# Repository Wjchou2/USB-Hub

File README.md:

# Endless' USB HUB

A compact custom USB 2.0 hub PCB based on the USB2514B controller. It features two USB-A ports and a 4-pin header breakout for easy integration with embedded systems or custom hardware projects.
Simply use a USB-C to C cable to plug the hub into your computer, and check that the LED indicator is on. Then connect any USB-A devices and they will show up on your computer.
I made this project because I have a Mac and never seem to have enough adapters, I also find that I use 4 pin headers often when tinkering with microcontrollers, so I added an easy access 4 pin header integrated into the hub. 

<br>
<br>
No firmware needed!

BOM:
| Designator  | Footprint                                               | Quantity | Designation                 | Link                                                                                                       | Cost   | Total Cost |
|-------------|---------------------------------------------------------|----------|-----------------------------|------------------------------------------------------------------------------------------------------------|--------|------------|
| U2          | SOT-223                                                 | 1        | AMS1117-3.3                 | https://www.lcsc.com/product-detail/C6186.html?s_z=n_AMS1117-3.3                                           | 0.1876 | 0.1876     |
| R3          | R_0603_1608Metric_Pad0.98x0.95mm_HandSolder             | 1        | 12k                         | https://www.lcsc.com/product-detail/C2906989.html?s_z=n_12k%25201%2525%25200603                            | 0.001  | 0.001      |
| R7,R6,R8,R9 | R_0603_1608Metric_Pad0.98x0.95mm_HandSolder             | 4        | 10k                         | https://www.lcsc.com/product-detail/C98220.html?s_z=n_10k%25201%2525%25200603                              | 0.0013 | 0.0052     |
| J2,J3       | USB_A_Receptacle_GCT_USB1046                            | 2        | USB_A                       | https://www.lcsc.com/product-detail/C6307429.html?s_z=n_USB1046                                            | 1.1405 | 2.281      |
| C2,C1,C7    | C_0805_2012Metric_Pad1.18x1.45mm_HandSolder             | 3        | 0.1µ                        | https://www.lcsc.com/product-detail/C53084456.html?s_z=n_100%2520nF%252050V%2520X7R%25200805               | 0.0018 | 0.0054     |
| C4,C3       | C_0603_1608Metric_Pad1.08x0.95mm_HandSolder             | 2        | 22 pF                       | https://www.lcsc.com/product-detail/C695385.html?s_z=n_22%2520pF%2520NPO%25200603                          | 0.051  | 0.102      |
| Y1          | Crystal_SMD_3225-4Pin_3.2x2.5mm                         | 1        | 12.000 MHz                  | https://www.lcsc.com/product-detail/C1647.html?s_z=n_18%2520pF%2520crysta                                  | 0.3272 | 0.3272     |
| J5          | PinHeader_1x04_P2.54mm_Vertical                         | 1        | Conn_01x04_Socket           | https://www.lcsc.com/product-detail/C52016392.html?s_z=n_Pin%2520Header%25201x04%25202.54mm                | 0.0171 | 0.0171     |
| R2,R1       | R_0603_1608Metric_Pad0.98x0.95mm_HandSolder             | 2        | 5.1k                        | https://www.lcsc.com/search?q=5.1k%25201%2525%25200603&s_z=n_5.1k%25201%2525%25200603                      | 0.0012 | 0.0024     |
| R4,R5       | R_0603_1608Metric_Pad0.98x0.95mm_HandSolder             | 2        | 100k                        | https://www.lcsc.com/product-detail/C14675.html?s_z=n_100k%25201%2525%25200603                             | 0.0013 | 0.0026     |
| C6,C5       | C_1206_3216Metric_Pad1.33x1.80mm_HandSolder             | 2        | 10 µF                       | https://www.lcsc.com/product-detail/C342827.html?s_z=n_10%2520uF%252016V%2520X7R%25201206                  | 0.0897 | 0.1794     |
| F1          | Fuse_1812_4532Metric_Pad1.30x3.40mm_HandSolder          | 1        | 0.5A                        | https://www.lcsc.com/product-detail/C7542969.html?s_z=n_PTC%2520fuse%25200.5A%25201812                     | 0.0403 | 0.0403     |
| J1          | USB_C_Receptacle_GCT_USB4105-xx-A_16P_TopMnt_Horizontal | 1        | USB_C_Receptacle_USB2.0_16P | https://www.lcsc.com/product-detail/C2988369.html?s_z=n_USB%2520C%2520receptacle%252016P%2520top%2520mount | 0.0829 | 0.0829     |
| U1          | QFN-36-1EP_6x6mm_P0.5mm_EP3.7x3.7mm                     | 1        | USB2514B_Bi                 | https://www.lcsc.com/product-detail/C220807.html?s_z=n_USB2514B%2520USB%2520hub%25204-port%2520Octopart    | 2.7952 | 2.7952     |
| R10         | R_0603_1608Metric_Pad0.98x0.95mm_HandSolder             | 1        | 1.5kΩ                       | https://www.lcsc.com/product-detail/C22843.html?s_z=n_1.5k%25201%2525%25200603                             | 0.0012 | 0.0012     |
| D1          | LED_0201_0603Metric_Pad0.64x0.40mm_HandSolder           | 1        | LED                         | https://www.lcsc.com/search?q=LED%25200603%2520Green&s_z=n_LED%25200603%2520Green                          | 0.0667 | 0.0667     |
|             |                                                         |          |                             |                                                                                                            |        | 6.0972     |

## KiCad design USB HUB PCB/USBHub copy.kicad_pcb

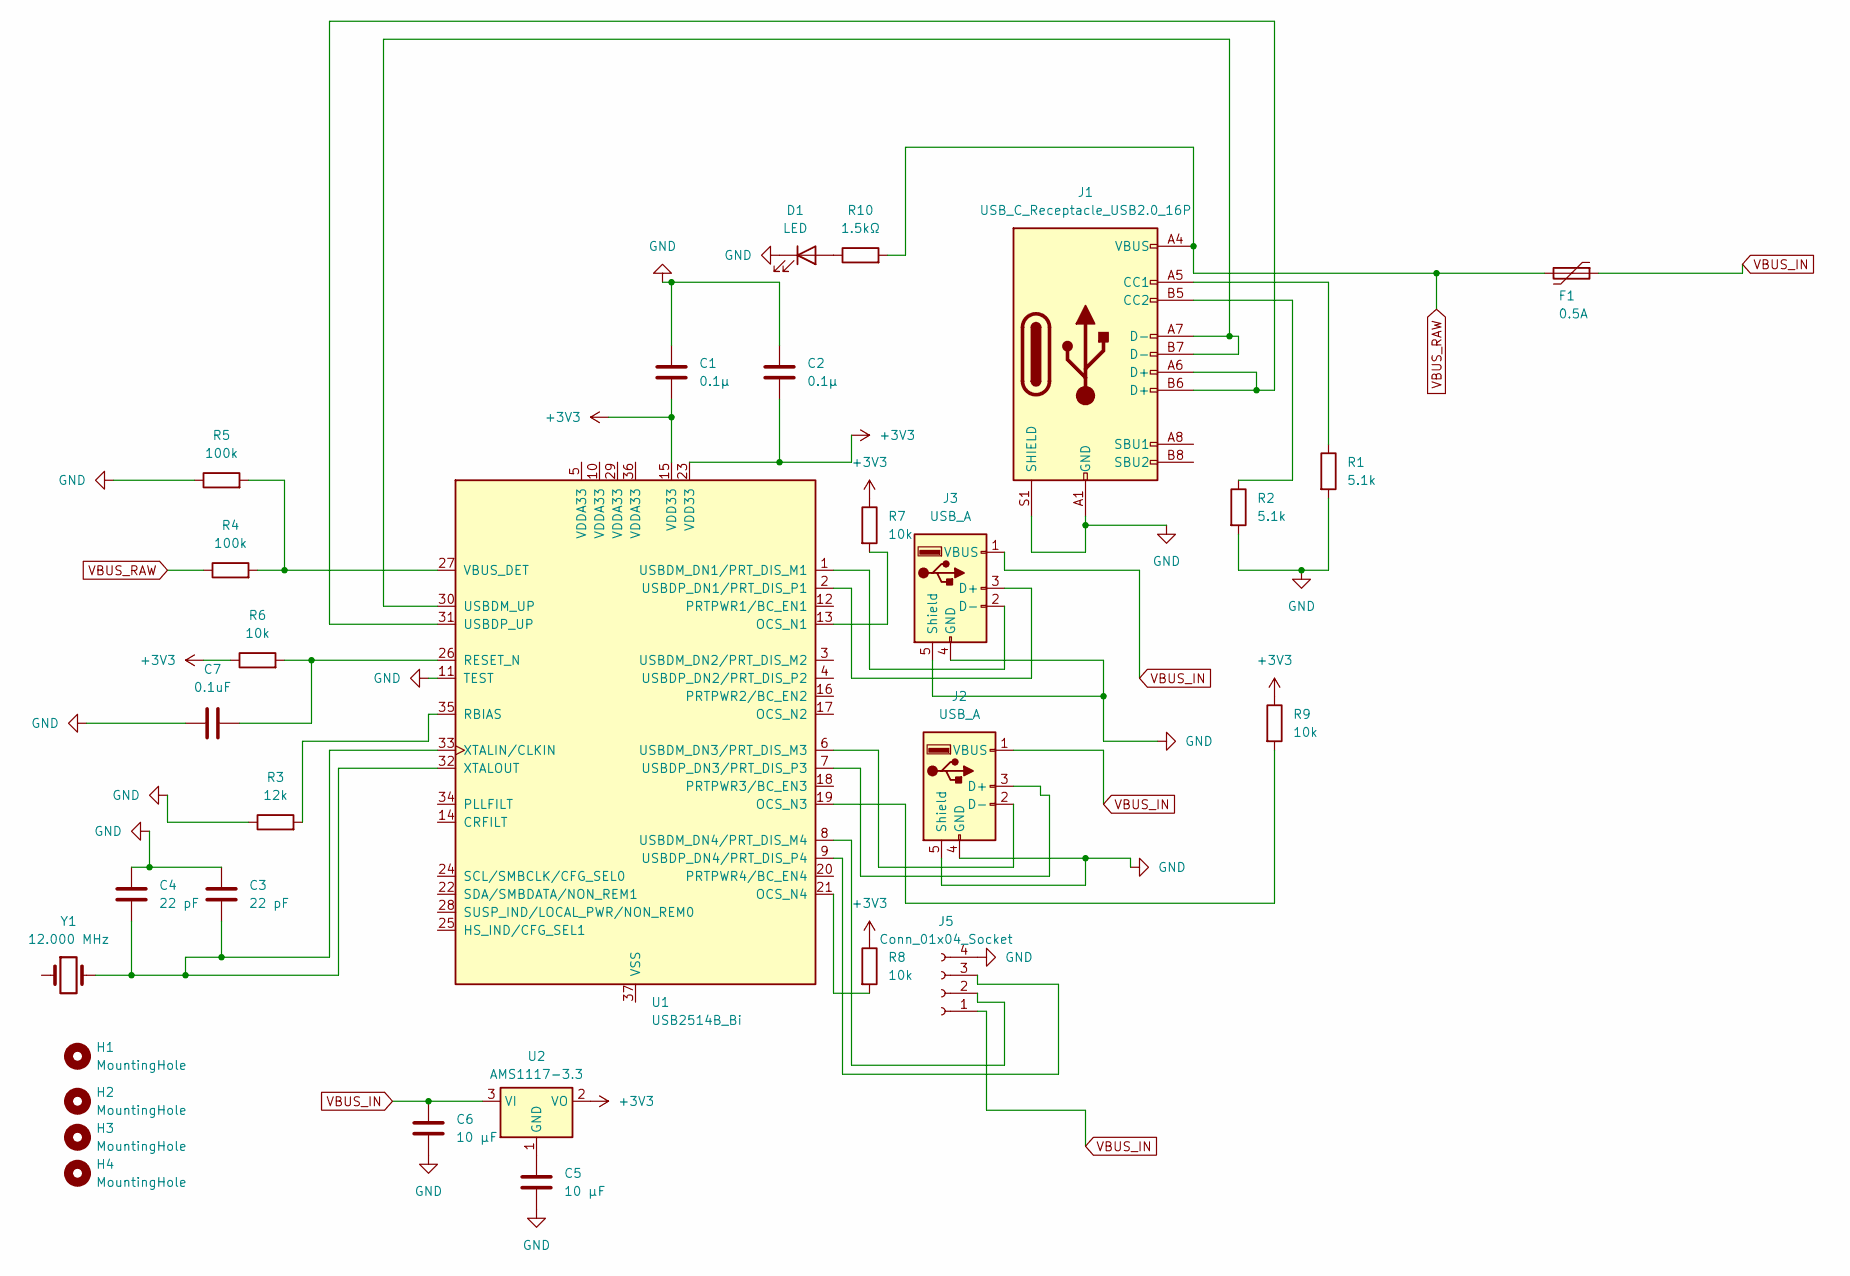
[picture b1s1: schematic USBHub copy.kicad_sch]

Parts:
C1, C2: 0.1µ; C_0805_2012Metric_Pad1.18x1.45mm_HandSolder
C3, C4: 22 pF; C_0603_1608Metric_Pad1.08x0.95mm_HandSolder
C5, C6: 10 µF; C_1206_3216Metric_Pad1.33x1.80mm_HandSolder
C7: 0.1uF; C_0805_2012Metric_Pad1.18x1.45mm_HandSolder
D1: LED; LED_0201_0603Metric_Pad0.64x0.40mm_HandSolder
F1: 0.5A; Fuse_1812_4532Metric_Pad1.30x3.40mm_HandSolder
H1, H2, H3, H4: MountingHole; MountingHole_2.2mm_M2
J1: USB_C_Receptacle_USB2.0_16P; USB_C_Receptacle_GCT_USB4105-xx-A_16P_TopMnt_Horizontal
J2, J3: USB_A; USB_A_Receptacle_GCT_USB1046
J5: Conn_01x04_Socket; PinHeader_1x04_P2.54mm_Vertical
R1, R2: 5.1k; R_0603_1608Metric_Pad0.98x0.95mm_HandSolder
R3: 12k; R_0603_1608Metric_Pad0.98x0.95mm_HandSolder
R4, R5: 100k; R_0603_1608Metric_Pad0.98x0.95mm_HandSolder
R6, R7, R8, R9: 10k; R_0603_1608Metric_Pad0.98x0.95mm_HandSolder
R10: 1.5kΩ; R_0603_1608Metric_Pad0.98x0.95mm_HandSolder
U1: USB2514B_Bi; QFN-36-1EP_6x6mm_P0.5mm_EP3.7x3.7mm
U2: AMS1117-3.3; SOT-223
Y1: 12.000 MHz; Crystal_SMD_3225-4Pin_3.2x2.5mm

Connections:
+3V3: C1.2, C2.2, R6.1, R7.1, R8.1, R9.1, U1.15 (VDD33), U1.23 (VDD33), U2.2 (VO)
GND: C1.1, C2.1, C3.1, C4.1, C5.2, C6.2, C7.1, D1.1 (K), J1.A1 (GND), J1.A12 (GND), J1.B1 (GND), J1.B12 (GND), J1.S1 (SHIELD), J2.4 (GND), J2.5 (Shield), J3.4 (GND), J3.5 (Shield), J5.4, R1.2, R2.2, R3.1, R5.1, U1.11 (TEST)
unnamed: D1.2 (A), R10.1
unnamed: J1.A5 (CC1), R1.1
unnamed: J1.B5 (CC2), R2.1
unnamed: J2.3 (D+), U1.7 (USBDP_DN3/PRT_DIS_P3)
unnamed: J2.2 (D-), U1.6 (USBDM_DN3/PRT_DIS_M3)
unnamed: J3.3 (D+), U1.2 (USBDP_DN1/PRT_DIS_P1)
unnamed: J3.2 (D-), U1.1 (USBDM_DN1/PRT_DIS_M1)
unnamed: J5.2, U1.8 (USBDM_DN4/PRT_DIS_M4)
unnamed: J5.3, U1.9 (USBDP_DN4/PRT_DIS_P4)
unnamed: R7.2, U1.13 (OCS_N1)
unnamed: R9.2, U1.19 (OCS_N3)
unnamed: R8.2, U1.21 (OCS_N4)
unnamed: R3.2, U1.35 (RBIAS)
unnamed: C7.2, R6.2, U1.26 (RESET_N)
unnamed: J1.A7 (D-), J1.B7 (D-), U1.30 (USBDM_UP)
unnamed: J1.A6 (D+), J1.B6 (D+), U1.31 (USBDP_UP)
unnamed: R4.2, R5.2, U1.27 (VBUS_DET)
unnamed: C3.2, C4.2, U1.32 (XTALOUT), U1.33 (XTALIN/CLKIN), Y1.2
unnamed: C5.1, U2.1 (GND)
VBUS_IN: C6.1, F1.1, J2.1 (VBUS), J3.1 (VBUS), J5.1, U2.3 (VI)
VBUS_RAW: F1.2, J1.A4 (VBUS), J1.A9 (VBUS), J1.B4 (VBUS), J1.B9 (VBUS), R4.1, R10.2

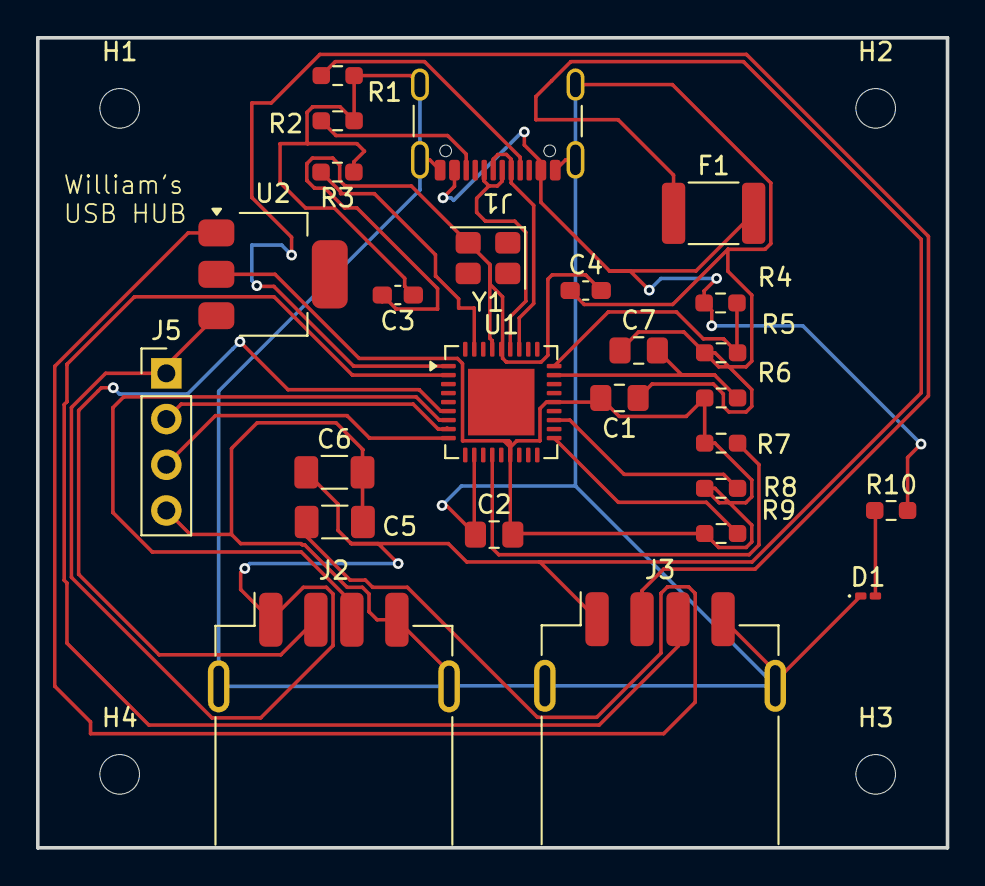
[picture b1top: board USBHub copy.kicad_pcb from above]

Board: 2 copper layers, 50.5 x 45.0 mm, 30 parts (0 on the bottom side), 23 nets.

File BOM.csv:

"","Designator","Footprint","Quantity","Designation","Link","Cost","Total Cost",""
"","-------------","---------------------------------------------------------","----------","-----------------------------","------------------------------------------------------------------------------------------------------------","--------","------------",""
"","U2","SOT-223","1","AMS1117-3.3","https://www.lcsc.com/product-detail/C6186.html?s_z=n_AMS1117-3.3","0.1876","0.1876",""
"","R3","R_0603_1608Metric_Pad0.98x0.95mm_HandSolder","1","12k","https://www.lcsc.com/product-detail/C2906989.html?s_z=n_12k%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","0.001","0.001",""
"","R7,R6,R8,R9","R_0603_1608Metric_Pad0.98x0.95mm_HandSolder","4","10k","https://www.lcsc.com/product-detail/C98220.html?s_z=n_10k%25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","0.0013","0.0052",""
"","J2,J3","USB_A_Receptacle_GCT_USB1046","2","USB_A","https://www.lcsc.com/product-detail/C6307429.html?s_z=n_USB1046","1.1405","2.281",""
"","C2,C1,C7","C_0805_2012Metric_Pad1.18x1.45mm_HandSolder","3","0.1µ","https://www.lcsc.com/product-detail/C53084456.html?s_z=n_100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","0.0018","0.0054",""
"","C4,C3","C_0603_1608Metric_Pad1.08x0.95mm_HandSolder","2","22 pF","https://www.lcsc.com/product-detail/C695385.html?s_z=n_22%25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","0.051","0.102",""
"","Y1","Crystal_SMD_3225-4Pin_3.2x2.5mm","1","12.000 MHz","https://www.lcsc.com/product-detail/C1647.html?s_z=n_18%2520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","0.3272","0.3272",""
"","J5","PinHeader_1x04_P2.54mm_Vertical","1","Conn_01x04_Socket","https://www.lcsc.com/product-detail/C52016392.html?s_z=n_Pin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","0.0171","0.0171",""
"","R2,R1","R_0603_1608Metric_Pad0.98x0.95mm_HandSolder","2","5.1k","https://www.lcsc.com/search?q=5.1k%25201%2525%25200603&s_z=n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","0.0012","0.0024",""
"","R4,R5","R_0603_1608Metric_Pad0.98x0.95mm_HandSolder","2","100k","https://www.lcsc.com/product-detail/C14675.html?s_z=n_100k%2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","0.0013","0.0026",""
"","C6,C5","C_1206_3216Metric_Pad1.33x1.80mm_HandSolder","2","10 µF","https://www.lcsc.com/product-detail/C342827.html?s_z=n_10%25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","0.0897","0.1794",""
"","F1","Fuse_1812_4532Metric_Pad1.30x3.40mm_HandSolder","1","0.5A","https://www.lcsc.com/product-detail/C7542969.html?s_z=n_PTC%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","0.0403","0.0403",""
"","J1","USB_C_Receptacle_GCT_USB4105-xx-A_16P_TopMnt_Horizontal","1","USB_C_Receptacle_USB2.0_16P","https://www.lcsc.com/product-detail/C2988369.html?s_z=n_USB%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","0.0829","0.0829",""
"","U1","QFN-36-1EP_6x6mm_P0.5mm_EP3.7x3.7mm","1","USB2514B_Bi","https://www.lcsc.com/product-detail/C220807.html?s_z=n_USB25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","2.7952","2.7952",""
"","R10","R_0603_1608Metric_Pad0.98x0.95mm_HandSolder","1","1.5kΩ","https://www.lcsc.com/product-detail/C22843.html?s_z=n_1.5k%2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","0.0012","0.0012",""
"","D1","LED_0201_0603Metric_Pad0.64x0.40mm_HandSolder","1","LED","https://www.lcsc.com/search?q=LED%25200603%2520Green&s_z=n_L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","0.0667","0.0667",""
"","","","","","","","6.0972",""
